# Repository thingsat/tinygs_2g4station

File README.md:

# TinyGS :: 2.4 GHz LoRa (low cost and low tech) ground station

Project to develop a ground station board that will receive messages from satellite on the 2.4GHz band. Satellite tracks are [Thingsat@STORK1](https://tinygs.com/satellite/ThingSat) and other cubeseat followed by the TinyGS community. This station is low cost (off the shelves boards and modules) and low tech (required only a solder iron).

This Git contains Hardware and software of a TinyGS 2.4 GHz LoRa ground station https://tinygs.com/.

## ESP32 Wroon 32U

The default MCU board is the [ESP32 Wroom 32U](https://www.espressif.com/sites/default/files/documentation/esp32-wroom-32d_esp32-wroom-32u_datasheet_en.pdf).

> Remark: The ESP32 Wroom 32D (on board PCB antenna) and The ESP32 Wroom 32U (UFL connector for an mandatory external antenna) can be used.

## SX1280 modules

For the long-range communication, we will use the Semtech SX1280, which is a low power 2.4 GHz LoRa RF Transceiver.

Several manufacturers provide RF modules integrating the SX1280 transceiver :
* [Lambda80 module](https://fr.farnell.com/rf-solutions/lambda80-24s/transceiver-2mbps-2-5ghz/dp/2988571)
* [EByte E28 module](https://www.amazon.com/Ebyte-%C3%89metteur-r%C3%A9cepteur-Bluetooth-E28-2G4M12S-%C3%A9metteur/dp/B07P2BZW5C)
* [SX1280PATR24 module](https://fr.aliexpress.com/item/1005001598235704.html) 
* [Miromico FMLR STM SX1280 module](https://miromico.ch/portfolio/fmlr-8x-x-stlx/?lang=en)
* [NiceRF LoRa1280 module](https://www.nicerf.com/products/detail/2-4ghz-lora-wireless-transceiver-module-lora1280-lora1281.html)
* [NiceRF LoRa1280-TCXO module](https://www.nicerf.com/products/detail/2-4ghz-range-measurement-wirelessly-long-distance-module-lora1280-tcxo.html)
* [NiceRF LoRa1280F27-TCXO module](https://www.nicerf.com/products/detail/500mw-2-4ghz-lora-wireless-transceiver-module-lora1280f27-tcxo.html)
* [Embit EMB-LR1280S](http://www.embit.eu/products/wireless-modules/emb-lr1280s/)

Project contains several PCBs and firmwares. 

##  Main Board

PCB are made to integrate up to 2 Mikrobus modules including SX1280 technology. Mikrobus board is an add-on board socket standard made by [mikroe](https://www.mikroe.com/mikrobus). This makes the ground station adjustable and modular.

There are 2 different PCB version:
* Board_Tinysgs_2.4GHz_V1, which contains: ESP32 Wroom 32 + 2 Mikrobus modules + Grove connectors (RXTX,I2C,ANA)
* Board_Tinysgs_2.4GHz_V2, which contains: ESP32 Wroom 32 + 2 Mikrobus modules + Grove connectors (RXTX,I2C,ANA) + H-Bridges for driving stepper + Power supply

We made the board as modular as possible. It is possible to implement all modules as desired, as long as it respects the Mikrobus pin specification. Mikrobus module are connected by SPI, I2C, UART and more GPIO. They are both supplied by 3V and Mikrobus_1 is also supplied by 5V if desired. 2 SMA connector mount edge are available on board. Theyre a connected to a SMA male connector, which allows to plug any signal that we want through a SMA female connector.

Both Mikrobus boards are connected to the ESP 32 by SPI. They are using the same SPI bus (SPI_0).

PCB are made on [KiCad](https://www.kicad.org/), which is a free software for electronics circuit board design. PCBs has been manufactered by [JLCPCB](https://jlcpcb.com/).

##  Power

A [Power Bank NCR18650B Battery shield](https://www.amazon.com/Diymore-Lithium-Battery-Charging-Arduino/dp/B07SZKNST4) made for Arduino and ESP32 can be plugged under the board using the 4 screw holes.

##  Mikrobus adapters for SX1280 modules

The design of two Mikrobus adapters for SX1280 modules are currently provided by the project:

* [Lambda80 SX1280 module adapter](./Mikrobus_Board_Lambda80C/)
* [EByte E28 SX1280 module adapter](./Mikrobus_Board_EbyteE28/)
* [NiceRF_SX1280_TCXO SX1280 module adapter](./Board_Mikrobus_NiceRF_1280_TCXO/)

The pinouts of those adapters have some differences.

> Two versions of the E28 module exists: 12S & 20S

```
EByte28 module
AN  <-> Busy
INT <-> DIO1
PWM <-> DIO2

Lambda80C module
AN  <-> DIO1
INT <-> Busy
PWM <-> DIO2

NiceRF SX1280 TCXO module
AN  <-> ??
INT <-> ??
PWM <-> ??
```

##  Other Mikrobus adapters for SX1280 modules

* [ ] [Geditech](https://www.geditech.fr/)'s LoRa SX1280 adapter
* [ ] [Stuart Robinson's (GW7HPW) Breadboard Friendly Board for NiceRF SX1280 Module](https://www.tindie.com/products/stuartsprojects/breadboard-friendly-board-for-nicrf-sx1280-module/)
* [ ] [Stuart Robinson's (GW7HPW) Breadboard Friendly Board for Ebyte E28 Module](https://www.tindie.com/products/stuartsprojects/breadboard-friendly-board-for-ebyte-e28-module/)

## Other Mikrobus modules (for the second Mikrobus slot)

Have a look into the [shop](https://www.mikroe.com/shop)

* [ ] [Geditech](https://www.geditech.fr/)'s LoRa Microchip RN2483 (for 433 MHz and 868 MHz ISM bands)

## Firmware

Firmware are into [./Firmware](./Firmware).

## Off-the-shelves gateways for LoRa 2.4 GHz

Those gateways had 3 LoRa® 2.4GHz channels for Rx and 1 LoRa® 2.4GHz channels for Tx.

* [Multitech MTCDT + MCard MTAC-LORA-2G4-3](https://www.multitech.net/developer/software/lora/mtac-lora-2g4-3/)
* [SX1280Z3DSFGW1 LoRa® 2.4GHz 3 Channels Single SF Reference Design](https://fr.semtech.com/products/wireless-rf/lora-24ghz/sx1280zxxxxgw1) (included a removable mPCIe card).
* [Embit EMB-FEM2GW-O-2G4](http://www.embit.eu/products/gateways-2/emb-fem2gw-o-2g4/) (included a removable mPCIe card EMB-LR1280-mPCIe-4x).

## References

* [ESP32-DevKitC V4 Getting Started Guide](https://docs.espressif.com/projects/esp-idf/en/latest/esp32/hw-reference/esp32/get-started-devkitc.html)
* [ESP32 Wroom 32 D/U Datasheet](https://www.espressif.com/sites/default/files/documentation/esp32-wroom-32d_esp32-wroom-32u_datasheet_en.pdf)

## Buy

### ESP32 Wroon 32U

* [ESP32-DevKitC-32U @ Aliexpress](https://fr.aliexpress.com/wholesale?SearchText=ESP32+Wroom+32U)
* [ESP32-DevKitC-32U @ Mouser](https://www.mouser.fr/ProductDetail/Espressif-Systems/ESP32-DevKitC-32U?qs=%252BEew9%252B0nqrCEVvpkdH%2FG5Q==)
* [ESP32-DevKit-LiPo @ Olimex](https://www.olimex.com/Products/IoT/ESP32/ESP32-DevKit-LiPo/open-source-hardware)

> **Important: ESP32 Wroon 32U had 38 pins and an UFL connector for an external (high gain and directive) antenna. ESP32 Wroon 32D had 38 pins and a PCB antenna. Choose ESP32 Wroon 32U for a better link margin.**

### SX1280 modules

* [LAMBDA80C-24D @ Farnell](https://fr.farnell.com/rf-solutions/lambda80c-24d/transceiver-2mbps-2-5ghz/dp/2988574?st=lambda80) (UFL connector + EM shield)
* [LAMBDA80C-24S @ Mouser](https://www.mouser.fr/ProductDetail/RF-Solutions/LAMBDA80C-24S?qs=17u8i%2FzlE89dhjIrlJ9FHg%3D%3D) (UFL connector + EM shield)
* [EByte E28-2G4M20S @ Aliexpress](https://fr.aliexpress.com/item/1005001812057589.html) (UFL connector + EM shield)

### PCB

* [Wuerth Elektronik](https://www.we-online.com/web/fr/wuerth_elektronik/start.php) 
* [JLCPCB](https://jlcpcb.com/)

### Headers and connectors
* [20-pin stackable headers (x2)](https://www.mouser.fr/ProductDetail/SparkFun/PRT-14311?qs=sGAEpiMZZMv0NwlthflBiwoz7B0w9MUDoIB50flBSMs%3D) for ESP32 : should be resized to 19 pins.
* [8-pin stackable headers (x2)](https://www.mouser.fr/ProductDetail/SparkFun/PRT-10007?qs=sGAEpiMZZMvShe%252BZiYheitG2EllKzxS98FBwaVjriqQ%3D) for Mikrobus modules.
* [Grove connectors (x3 but optional)](https://www.mouser.fr/ProductDetail/Seeed-Studio/110990030?qs=1%252B9yuXKSi8Dw9fpnq%252BdNzQ%3D%3D).

### Power (Optional)
* [Diymore 2x18650 Battery Pack @ Aliexpress](https://fr.aliexpress.com/item/33016661427.html)
* [DFRobot Solar Power Manager 5V](https://www.dfrobot.com/product-1712.html)
* [DFRobot Solar Power Manager Micro](https://www.dfrobot.com/product-1781.html)
* [Adafruit Universal USB / DC / Solar Lithium Ion/Polymer charger - bq24074](https://learn.adafruit.com/adafruit-bq24074-universal-usb-dc-solar-charger-breakout/design-notes)

### Power Profiling
* [Nordic Power Profiler Kit II](https://github.com/CampusIoT/tutorial/tree/master/nrf-ppk2#readme)
> Plug the PPK2 power source (`VOUT`+`GND`) on `3V3`+`GND` pin (double-row header and Grove connectors) and DO NOT plug the ESP32 throught the mini-USB connector.

### Debbuging
* [ ] [Click Analyzer](https://www.mikroe.com/click-analyzer)

## 2.4 GHz antennas
* [SuperAntennaz](https://wiki.satnogs.org/SuperAntennaz)
* [DIY Quadrifilar Helix Antenna for 2450 MHz](https://www.thingiverse.com/thing:634205)
* [Sirio SDC-2.4-15](https://www.sirioantenne.it/en/products/wlan/sdc-2-4-15): Directional, Linear Vertical or Horizontal Polarization, 12.9 dBd – 15 dBi.
  
## Licenses

For PCB designs, the license is [Attribution-NonCommercial-ShareAlike 4.0 International (CC BY-NC-SA 4.0)](https://creativecommons.org/licenses/by-nc-sa/4.0/).

For Software, check the license into each directory.

## Todolist

* [x] PCB for ESP32 Wroom 32 (38 pins) + 2 Mikrobus modules + 3 groves connectors (RXTX,I2C,ANA)
* [ ] PCB for ESP32 Wroom 32 (38 pins) + 2 Mikrobus modules + 3 groves connectors (RXTX,I2C,ANA) + H-Bridges for driving stepper + Power supply
* [x] Mikrobus adapter for Lambda80 SX1280 module
* [x] Mikrobus adapter for EByte E28 SX1280 module
* [ ] Mikrobus adapter for [SX1280PATR24 module](https://fr.aliexpress.com/item/1005001598235704.html) 
* [ ] Mikrobus adapter for [Miromico FMLR STM SX1280 module](https://miromico.ch/portfolio/fmlr-8x-x-stlx/?lang=en)
* [ ] Mikrobus adapter for [NiceRF SX1280 module](https://stuartsprojects.github.io/2019/10/07/2-4ghz-nicerf-sx1280-lora-balloon-tracker-85km-achieved.html)
* [ ] Mikrobus adapter for [Microchip RN2483 module](https://www.microchip.com/en-us/product/RN2483)
* [ ] Mikrobus adapter for [RF Solutions RF-LORA-868-SO module](https://fr.rs-online.com/web/p/lpwan/9033059)
* [ ] Mikrobus adapter for [Abeeway-Murata Geolocation Module](https://docs.abeeway.com/thingpark-location/B-Feature-Topics/GeolocModule_C/)
* [ ] Mikrobus protoshield
* [x] [Arduino sketches](./Firmware/Arduino/SX1280) for ESP32 Wroom 32 + E28 Mikrobus module
* [x] [Arduino sketches](./Firmware/Arduino/SX1280) for ESP32 Wroom 32 + Lambda80 Mikrobus module
* [ ] [Arduino sketches](./Firmware/Arduino/SX1280) for Wio Terminal + Lambda80 Mikrobus module
* [ ] Move UART Grove connector for using Grove cable with ESP32-WROOM-32D (PCB antenna)
* [ ] TinyGS firmware for ESP32 Wroom 32 + E28 Mikrobus module
* [ ] TinyGS firmware for ESP32 Wroom 32 + Lambda80 Mikrobus module
* [ ] TinyGS firmware for ESP32 Wroom 32 + [Miromico FMLR STM SX1280 module](https://miromico.ch/portfolio/fmlr-8x-x-stlx/?lang=en)
* [ ] TinyGS firmware for ESP32 Wroom 32 + [LR1120 Dev Kit module](https://fr.semtech.com/products/wireless-rf/lora-edge/lr1120dvk1tbks) for such modulations and bands : LoRa SubGHz, LoRa 2.4GHz, LR-FHSS, S-Band (1.9-2.1GHz)
* [ ] TinyGS firmware for [Wio Terminal](https://wiki.seeedstudio.com/Wio-Terminal-Getting-Started/) + Lambda80 Mikrobus module
* [ ] Power consumption study with [X-NUCLEO-LPM01A](https://www.st.com/en/evaluation-tools/x-nucleo-lpm01a.html)
* [ ] RIOTOS firmware for ESP32 Wroom 32 + Lambda80 module (cubesat emulator)
* [ ] Test the [Geditech](https://www.geditech.fr/)'s LoRa Microchip RN2483 (for 433 MHz and 868 MHz ISM bands) on second slot.
* [ ] Add slots for I2C and UART grove connectors into the two Mikrobus slots (can be used when the Mikrobus slot is not used)
* [ ] Add slot for female header in order to plug a low-cost SDCard SPI breakout (useful for data logging)
* [ ] Add slot for female/male header in order to plug a low-cost DS1307/DS3231 breakout (useful for timestamping data log entries)
* [ ] Add extra slot for power sources (3V3, VCC)
* [ ] Add white label for DevEUI and serial number on silkscreen layer
* [ ] Add pin for IRQ on [GNSS PPS](https://en.wikipedia.org/wiki/Pulse-per-second_signal)
* [ ] Design Fritzing part for the station
* [x] add licenses
* [ ] review PCB designs according the [Mikrobus specifications v2.0](https://download.mikroe.com/documents/standards/mikrobus/mikrobus-standard-specification-v200.pdf)
* [ ] add L9616 CAN driver footprint ([see](https://copperhilltech.com/blog/can-bus-development-with-esp32wroom32-development-board/)) connected to `CAN_TXD = ESP32 – IO25` and `CAN_RXD = ESP32 – IO26`

## Media

Here the picture of the board_V1, with or without modules. On last picture, a GPS, a magnetometer and a joystick are connected by grove connection.

Mounted PCB with Grove boards ([Grove Thumb Joystick](https://wiki.seeedstudio.com/Grove-Thumb_Joystick/), [Grove  LSM6DS3 Accelerometer Gyroscope](https://wiki.seeedstudio.com/Grove-6-Axis_AccelerometerAndGyroscope/), [Grove GPS](https://wiki.seeedstudio.com/Grove-GPS/)) and Lamdba80 and E28 module.

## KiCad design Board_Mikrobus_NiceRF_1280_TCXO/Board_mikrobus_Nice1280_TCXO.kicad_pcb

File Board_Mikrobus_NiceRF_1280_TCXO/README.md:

# Mikrobus adapter for [NiceRF 1280 TCXO module](https://www.nicerf.com/sx1280/)

Designed by [Nicolas Nohlier](https://www.linkedin.com/in/nicolas-nolhier-127b4a61/?originalSubdomain=fr) ([F5MDY](https://fr.aprs.fi/info/a/F5MDY-B)), [CSUT](https://www.csut.cnrs.fr/) & LAAS.

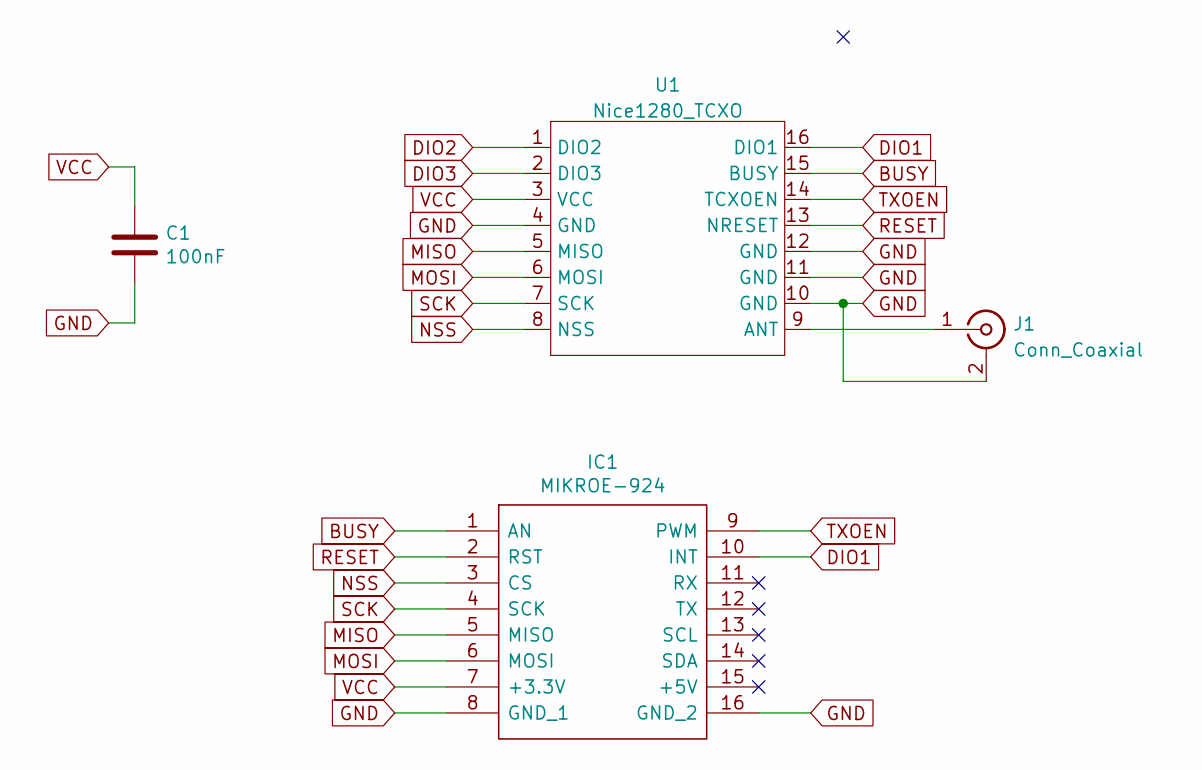
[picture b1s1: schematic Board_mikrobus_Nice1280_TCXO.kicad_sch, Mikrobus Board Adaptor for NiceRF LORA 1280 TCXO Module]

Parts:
C1: 100nF; C_0805_2012Metric_Pad1.18x1.45mm_HandSolder
IC1: MIKROE-924; MIKROE924; Manufacturer_Part_Number MIKROE-924; Mouser Part Number 932-MIKROE-924
J1: Conn_Coaxial; U.FL_Molex_MCRF_73412-0110_Vertical
U1: Nice1280_TCXO; HOPERF_RFM9XW_SMD

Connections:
BUSY: IC1.1 (AN), U1.15 (BUSY)
DIO1: IC1.10 (INT), U1.16 (DIO1)
DIO2: U1.1 (DIO2)
DIO3: U1.2 (DIO3)
GND: C1.2, IC1.8 (GND_1), IC1.16 (GND_2), J1.2 (Ext), U1.4 (GND), U1.10 (GND), U1.11 (GND), U1.12 (GND)
MISO: IC1.5 (MISO), U1.5 (MISO)
MOSI: IC1.6 (MOSI), U1.6 (MOSI)
NSS: IC1.3 (CS), U1.8 (NSS)
unnamed: J1.1 (In), U1.9 (ANT)
RESET: IC1.2 (RST), U1.13 (NRESET)
SCK: IC1.4 (SCK), U1.7 (SCK)
TXOEN: IC1.9 (PWM), U1.14 (TCXOEN)
VCC: C1.1, IC1.7 (+3.3V), U1.3 (VCC)

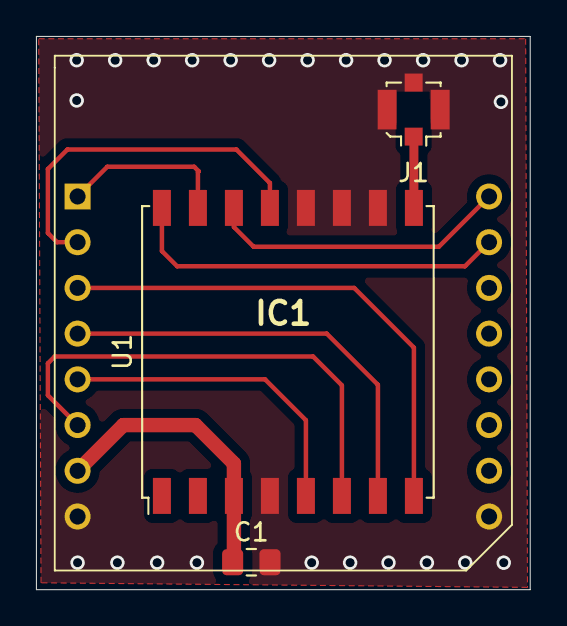
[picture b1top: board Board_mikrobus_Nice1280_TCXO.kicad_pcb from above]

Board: 2 copper layers, 27.4 x 30.7 mm, 4 parts (0 on the bottom side), 11 nets.

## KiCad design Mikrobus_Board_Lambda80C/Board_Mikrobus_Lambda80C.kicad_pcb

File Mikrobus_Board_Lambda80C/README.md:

# Mikrobus Adapter for Lambda80-24S SX1280 Module

This is a board to support a lambda80C 2.4GHz LORA transceiver RF module, adapted to Mikrobus standard pinout specification.

Lambda Module used: [Lambda80-24S](https://fr.farnell.com/rf-solutions/lambda80-24s/transceiver-2mbps-2-5ghz/dp/2988571). The LAMBDA80 is a 2.4GHz LoRa transceiver using the Semtech SX1280 technology, providing ultra-long range, spread spectrum communication and high interference immunity within minimal current. For more information on [SX1280](https://github.com/thingsat/tinygs_2g4station/blob/main/Datasheet_SEMTECH_SX1280.PDF).

Some Specification:
* Transmit power +12.5 dBm
* High sensitivity: down to -132 dBm
* RF Data Rate: FSK upto 2.02Mbps - LoRa upto 476bps

Programing of the module is via SPI interface. This module has as pin BUSY, RESET, SPI, 3 DIO (Digital I/O software configured) and a Antenna connection “C” Versions. Antenna  is connectable with a connector UFL female.

Here the connection between the Mikrobus standard pin and the Lambda80 module pin

	AN	<->	DIO1
	RST	<->	RESET
	CS	<->	NSEL
	SCK	<->	SCLK
	MISO	<->	SDO
	MOSI	<->	SDI
	PWM	<->	DIO2
	INT	<->	BUSY

Lambda80 is supplied with 3.3V, by the +3.3V Mikrobus pin.

The Ebyte E28 module has no PCB antenna, so a external antenna is needed. A UFL male connector is available on the module to plug a external antenna with a UFL female connector.

### Kicad Project
The project was made on Kikad, which is a free software for electronics circuit board design, developed by IUT of Grenoble.

For the mikrobus lib and footprint, I use the [MIKROE-924](https://componentsearchengine.com/part-view/MIKROE-924/MIKROELEKTRONIKA) model available on [component search engine](https://componentsearchengine.com/).
For the Lambda80, I use the [Lambda80](https://componentsearchengine.com/part-view/LAMBDA80-24S/RF%20SOLUTIONS) model.

All the schematic and footprint are in the "Lib & Fp" folder. For the Mikrobus and Lambda80 lib, you have to choose the KiCad folder when adding the lib to the project.

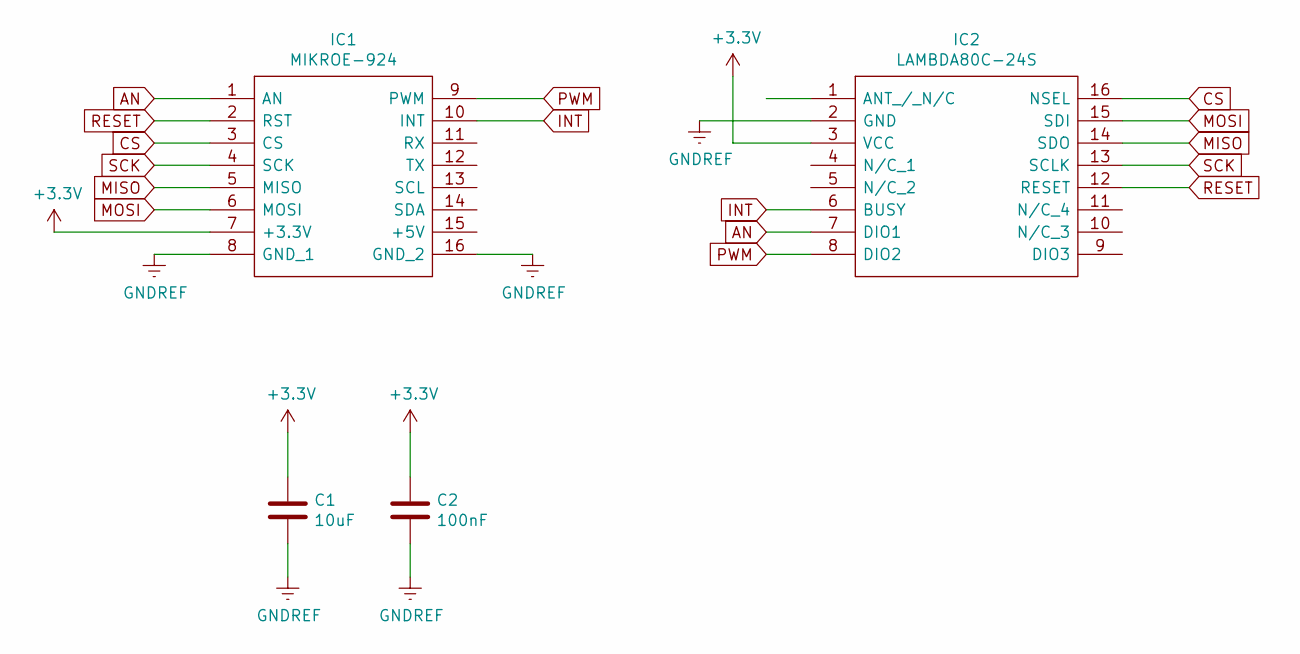
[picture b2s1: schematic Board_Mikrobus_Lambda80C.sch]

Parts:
C1: 10uF; C_0805_2012Metric
C2: 100nF; C_0805_2012Metric
IC1: MIKROE-924; MIKROE924; Manufacturer_Part_Number MIKROE-924; Mouser Part Number 932-MIKROE-924
IC2: LAMBDA80C-24S; Lambda80C_24S-traversant; Manufacturer_Part_Number LAMBDA80C-24S; Mouser Part Number 223-LAMBDA80C-24S

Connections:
+3V3: C1.1, C2.1, IC1.7 (+3.3V), IC2.3 (VCC)
AN: IC1.1 (AN), IC2.7 (DIO1)
CS: IC1.3 (CS), IC2.16 (NSEL)
GNDREF: C1.2, C2.2, IC1.8 (GND_1), IC1.16 (GND_2), IC2.2 (GND)
INT: IC1.10 (INT), IC2.6 (BUSY)
MISO: IC1.5 (MISO), IC2.14 (SDO)
MOSI: IC1.6 (MOSI), IC2.15 (SDI)
PWM: IC1.9 (PWM), IC2.8 (DIO2)
RESET: IC1.2 (RST), IC2.12 (RESET)
SCK: IC1.4 (SCK), IC2.13 (SCLK)

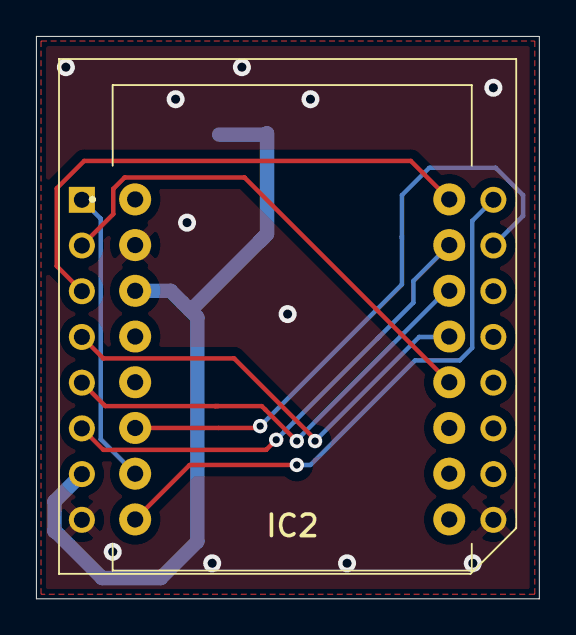
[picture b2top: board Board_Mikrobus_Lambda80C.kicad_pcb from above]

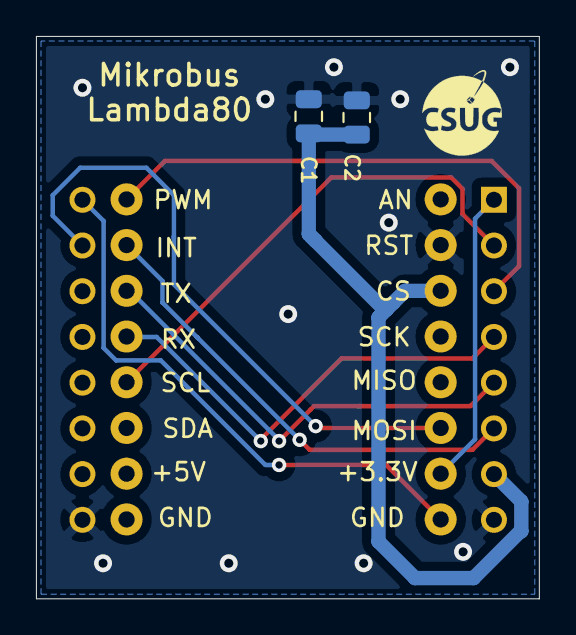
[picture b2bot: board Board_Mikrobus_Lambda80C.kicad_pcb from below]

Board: 2 copper layers, 27.9 x 31.2 mm, 4 parts (2 on the bottom side), 10 nets.

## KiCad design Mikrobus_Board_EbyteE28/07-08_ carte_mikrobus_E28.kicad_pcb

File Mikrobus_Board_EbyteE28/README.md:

# Mikrobus Adapter for Ebyte E28 SX1280 Module

This is a board to support a Ebyte E28 2.4GHz LORA transceiver RF module, adapted to Mikrobus standard pinout specification. This board will allow you to use your Ebyte E28-2G4M module with a standard 0.1” matrix breadboard or a Mikrobus Standard.

The Ebyte E28-2G4M is a RF transceiver module using the Semtech SX1280 LoRa technology, operate in 2.400 ~ 2.500GHz with ultra-low power consumption. More information available on [Ebyte site](https://www.ebyte.com/en/product-view-news.html?id=286). 

This board can support E28_2G4M12S and E28_2G4M20S. This Ebyte E28 Board is inspired by the [Breadboard Friendly Ebyte E28 Board](https://github.com/StuartsProjects/Devices/tree/master/Breadboard%20Friendly%20EbyteE28%20Board) made by StuartsProjects.

Ebyte E28 module usable: [Ebyte E28-2G4M12S](https://www.amazon.fr/Ebyte-%C3%89metteur-r%C3%A9cepteur-Bluetooth-E28-2G4M12S-%C3%A9metteur/dp/B07P2BZW5C) / [Ebyte E28-2G4M20S](https://www.amazon.fr/EBYTE-E28-2G4M20S-SX1280-%C3%89metteur-R%C3%A9cepteur/dp/B07R77CKFK). They are the same module, exept that the E28-2G4M20S as 2 more Pins (14 pin for 12S and 16 pin for 20S).These extra pins are for Rx/Tx connection for PA and LNA control.

Here the connection between the Mikrobus standard pin and the E28 module pin

	AN	<->	Busy
	RST	<->	NRESET
	CS	<->	NSS_CTS
	SCK	<->	SCK_RTS
	MISO	<->	MISO_TX
	MOSI	<->	MOSI_RX
	PWM	<->	DIO2
	INT	<->	DIO1
	
	for M20S
	Rx	<->	TX_EN
	Tx	<->	RX_EN

Ebyte E28 is supplied with 3.3V, by the +3.3V Mikrobus pin.

The Ebyte E28 module has a PCB antenna, so no external antenna is needed, but the here also a SMA connector to use a external antenna.

## Kicad Project
The project was made on Kikad, which is a free software for electronics circuit board design, developed by IUT of Grenoble.

For the mikrobus lib and footprint, I use the [MIKROE-924](https://componentsearchengine.com/part-view/MIKROE-924/MIKROELEKTRONIKA) model available on [component search engine](https://componentsearchengine.com/).
For the E28 schematic and footprint, I found nothing on internet so I made my own. 

All the schematic and footprint are in the "Lib & Fp" folder. For the Mikrobus lib, you have to choose the KiCad folder.

## TODO

* [ ] Move module in order to place the PCB antenna outside of the adapter.

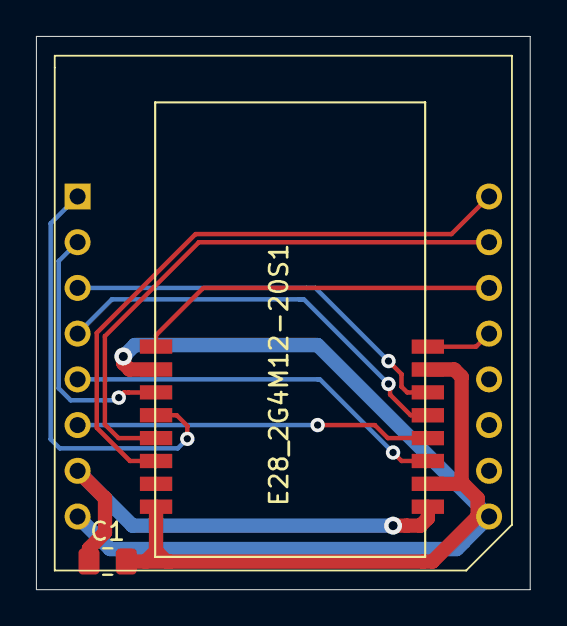
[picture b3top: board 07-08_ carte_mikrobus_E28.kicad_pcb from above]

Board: 2 copper layers, 27.4 x 30.7 mm, 3 parts (0 on the bottom side), 12 nets.

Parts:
C1: 100nF; C_0805_2012Metric_Pad1.18x1.45mm_HandSolder
E28_2G4M12-20S1: E28; E28-2G4M12-20S
IC1: MIKROE-924; MIKROE924

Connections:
BUSY: E28_2G4M12-20S1.12, IC1.1
DIO1: E28_2G4M12-20S1.13, IC1.10
DIO2: E28_2G4M12-20S1.14, IC1.9
GND: C1.2, E28_2G4M12-20S1.2, E28_2G4M12-20S1.7, E28_2G4M12-20S1.10, E28_2G4M12-20S1.16, IC1.8, IC1.16
MISO: E28_2G4M12-20S1.3, IC1.5
MOSI: E28_2G4M12-20S1.4, IC1.6
NSS: E28_2G4M12-20S1.6, IC1.3
RESET: E28_2G4M12-20S1.11, IC1.2
RXEN: E28_2G4M12-20S1.8, IC1.12
SCK: E28_2G4M12-20S1.5, IC1.4
TXEN: E28_2G4M12-20S1.9, IC1.11
VCC: C1.1, E28_2G4M12-20S1.1, IC1.7

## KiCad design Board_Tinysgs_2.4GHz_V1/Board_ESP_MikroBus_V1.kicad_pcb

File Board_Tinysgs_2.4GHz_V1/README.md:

# Main Board for TinyGS 2.4GHz Station

This board is the firts version of the 2.4GHz gateway for [TinyGS](https://tinygs.com/).

Contain Schematic and PCB file for ESP32 Vroom + 2 Mikrobus modules + 2 groves connectors (RXTX,I2C).

This Board is designed to support a ESP32 devkitC-V4 and 2 MiKroBus modules. This board is the firts version of the 2.4GHz tinygs ground station gateway and named Board_V1

The purpose of this board is to control mikrobus modules including SX1280 technology that will transmit and receive messages on a 2.4GHz radio frequency. Each module are connected to a ESP32 which will be connected to the wifi.

Mikrobus board is an add-on board socket standard made by [mikroe](https://www.mikroe.com/mikrobus)

Connection between ESP32 - ESP32-DevKitC V4 and Mikrobus modules

MiKroBus 0:
	 				 
	SPI_0:
	CLK 	IO18
	MISO	IO19
	MOSI	IO23
	NSS(CS)	IO05
	
	UART_0	:
	Tx	IO01
	Rx	IO03
	
	I2C:
	SDA	IO21
	SCL	IO22
	
	AN_0	IO33
	RESET_0 IO32
	PWM_0	IO25
	INT_0	IO26

MiKroBus 1: 				 
	
	SPI_0
	CLK 	IO18
	MISO	IO19
	MOSI	IO23
	NSS 	IO15
	
	UART_2
	Tx	IO17
	Rx	IO16
	
	I2C:
	SDA	IO21
	SCL	IO22
	
	AN_1	IO27
	RESET_1 IO14
	PWM_1	IO04
	INT_1	IO13

Grove connector available on board :

	I2C:			UART_2(Rx/Tx):		GPIO(INPUT Only):
	SDA   IO21		Tx	IO17		IO34
	SCL   IO22		Rx	IO16		IO35

UART_2 can be connected to module MiKroBus 2 or to grove connector. A jumper need to be plug to choose beetween grove output or the mikrobus module.

Two UFL connected to a SMA mount edge connector are available to plug an antenna. They are disconnected from the rest of the board, which allows to connect the module that you want to the antenna, with a SMA -UFL connector.

A powerbank can be plug under the board to supply the 3V. The [powerbank](https://www.amazon.com/Diymore-Lithium-Battery-Charging-Arduino/dp/B07SZKNST4) is design for ESP32 and is purchasable on amazon. 
5V is only available on the Mikrobus 1 module. 

Careful:
* UART0 is used for flashing and debuging. Be very careful to its use.
* GPIO grove connector are INPUT only, ESP32wroom cannot write on this connection.
* Both Chip selec (NSS) for the SPI communication are Pulled HIGH (IO05 & IO15).
* No 5V on Mikrobus 0. 

## Library and footprint

Lib & empreinte folder contains all necessary symbol and footprint for the project:
* ESP32 symbol and footprint. Footprint has been changed to match with our ESP32-devkitC-V4
* Mikrobus (mikroe-2439) symbol and footprint
* Grove connector for I2C and RxTx connection
* SMA and UFL connector

## Files
* .pro: File containing the parameters of the project.
* .sch: Schema files.
* .kicad_pcb: Printed circuit board files.
* sym-info-cache: Library list file (symbol library table): declaration of component symbol libraries available for the schema editor.
* fp-lib-table: Library list file (footprint library table): declaration of component footprint libraries available for the PCB editor.

## Rendered

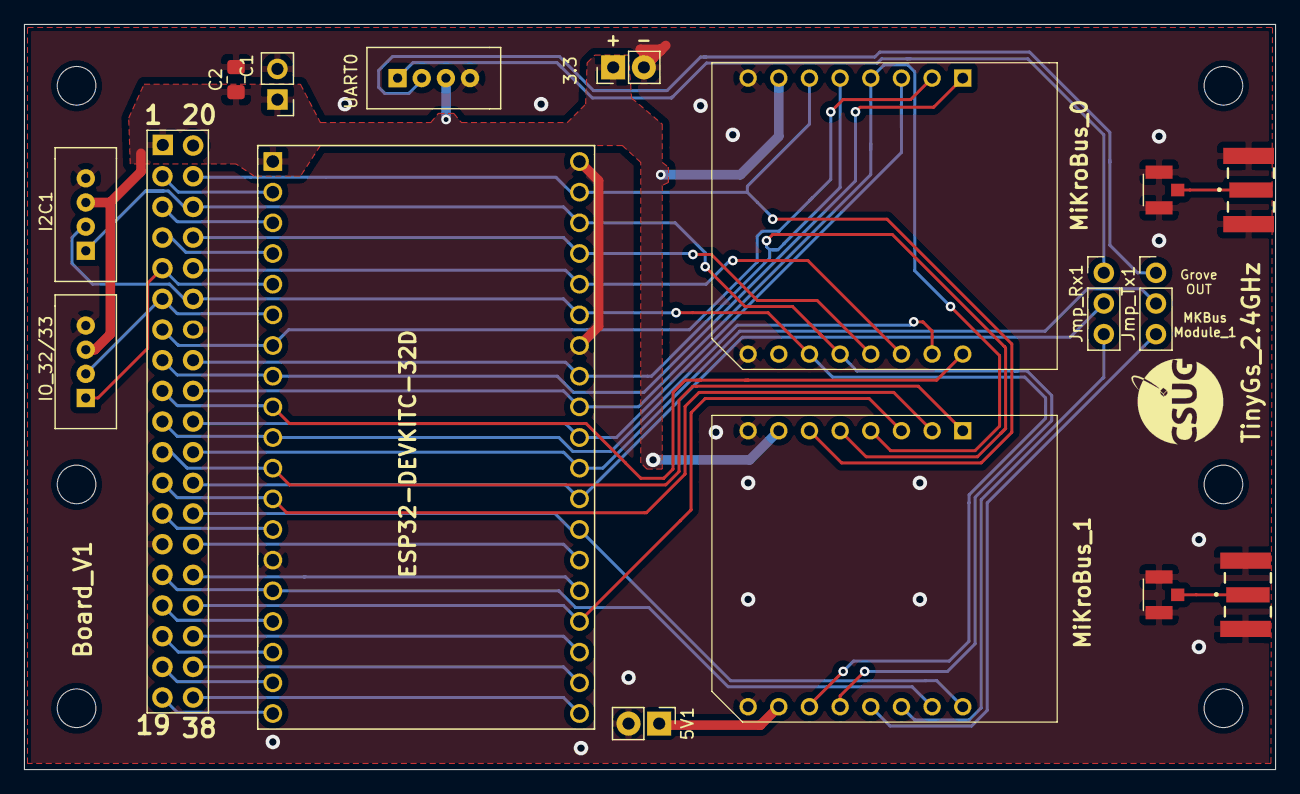
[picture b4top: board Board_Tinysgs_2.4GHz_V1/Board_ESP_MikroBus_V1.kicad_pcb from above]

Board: 2 copper layers, 103.6 x 61.7 mm, 17 parts (0 on the bottom side), 43 nets.

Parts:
3.3, 5V1: Conn_01x02; PinHeader_1x02_P2.54mm_Vertical
C1: C; PinHeader_1x02_P2.54mm_Vertical
C2: C; C_0805_2012Metric_Pad1.18x1.45mm_HandSolder
Connector_2x19: Conn_02x19_Top_Bottom; conn_2x19_2.54mm_top_bot
I2C1: Grove; Grove_4pin-2.00mm
IO_32/33: Grove; Grove_4pin-2.00mm
Jmp_Rx1: Jumper_NC_Dual; PinHeader_1x03_P2.54mm_Vertical
Jmp_Tx1: Jumper_NC_Dual; PinHeader_1x03_P2.54mm_Vertical
MiKroBus_0, MiKroBus_1: MIKROE-924; MIKROE924
SMA_1, SMA_2: SMA-J-P-H-ST-EM1; SAMTEC_SMA-J-P-H-ST-EM1
U1: ESP32-DEVKITC-32D; MODULE_ESP32-DEVKITC-V4-32D
UART0: Grove; Grove_4pin-2.00mm
UFL_1, UFL_2: U.FL-R-SMT(01); HRS_U.FL-R-SMT(01)

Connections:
+3V3: 3.3.1, C1.1, C2.1, Connector_2x19.1, I2C1.3, IO_32/33.3, MiKroBus_0.7, MiKroBus_1.7, U1.1, UART0.3
+5V: 5V1.1, MiKroBus_1.15
/2: Connector_2x19.2, U1.2
/3: Connector_2x19.3, U1.3
/4: Connector_2x19.4, U1.4
/13: Connector_2x19.13, U1.13
/16: Connector_2x19.16, U1.16
/17: Connector_2x19.17, U1.17
/18: Connector_2x19.18, U1.18
/19: Connector_2x19.19, U1.19
/33: Connector_2x19.33, U1.33
/34: Connector_2x19.34, U1.34
/36: Connector_2x19.36, U1.36
/37: Connector_2x19.37, U1.37
/38: Connector_2x19.38, U1.38
AN_0: Connector_2x19.8, MiKroBus_0.1, U1.8
AN_1: Connector_2x19.11, MiKroBus_1.1, U1.11
GNDREF: 3.3.2, 5V1.2, C1.2, C2.2, Connector_2x19.14, Connector_2x19.20, Connector_2x19.26, I2C1.4, IO_32/33.4, MiKroBus_0.8, MiKroBus_0.16, MiKroBus_1.8, MiKroBus_1.16, SMA_1.2_1, SMA_1.2_2, SMA_1.3_1, SMA_1.3_2, SMA_2.2_1, SMA_2.2_2, SMA_2.3_1, SMA_2.3_2, U1.14, U1.20, U1.26, UART0.4, UFL_1.1, UFL_1.2, UFL_2.1, UFL_2.2
I2C_SCL: Connector_2x19.22, I2C1.1, MiKroBus_0.13, MiKroBus_1.13, U1.22
I2C_SDA: Connector_2x19.25, I2C1.2, MiKroBus_0.14, MiKroBus_1.14, U1.25
IN34: Connector_2x19.5, IO_32/33.1, U1.5
IN35: Connector_2x19.6, IO_32/33.2, U1.6
INT_0: Connector_2x19.10, MiKroBus_0.10, U1.10
INT_1: Connector_2x19.15, MiKroBus_1.10, U1.15
MISO_0: Connector_2x19.27, MiKroBus_0.5, MiKroBus_1.5, U1.27
MOSI_0: Connector_2x19.21, MiKroBus_0.6, MiKroBus_1.6, U1.21
NSS_0: Connector_2x19.29, MiKroBus_0.3, U1.29
NSS_1: Connector_2x19.35, MiKroBus_1.3, U1.35
unnamed: SMA_1.1, UFL_1.3
unnamed: SMA_2.1, UFL_2.3
PWM_0: Connector_2x19.9, MiKroBus_0.9, U1.9
PWM_1: Connector_2x19.32, MiKroBus_1.9, U1.32
Reset_0: Connector_2x19.7, MiKroBus_0.2, U1.7
Reset_1: Connector_2x19.12, MiKroBus_1.2, U1.12
SCK_0: Connector_2x19.28, MiKroBus_0.4, MiKroBus_1.4, U1.28
UART0_Rx: Connector_2x19.24, MiKroBus_0.11, U1.24
UART0_Tx: Connector_2x19.23, MiKroBus_0.12, U1.23
UART2_Rx: Connector_2x19.31, Jmp_Rx1.2, U1.31
UART2_Rx_MiKroBus: Jmp_Rx1.3, MiKroBus_1.11
UART2_Rx_grove: Jmp_Rx1.1, UART0.1
UART2_Tx: Connector_2x19.30, Jmp_Tx1.2, U1.30
UART2_Tx_MiKroBus: Jmp_Tx1.3, MiKroBus_1.12
UART2_Tx_grove: Jmp_Tx1.1, UART0.2

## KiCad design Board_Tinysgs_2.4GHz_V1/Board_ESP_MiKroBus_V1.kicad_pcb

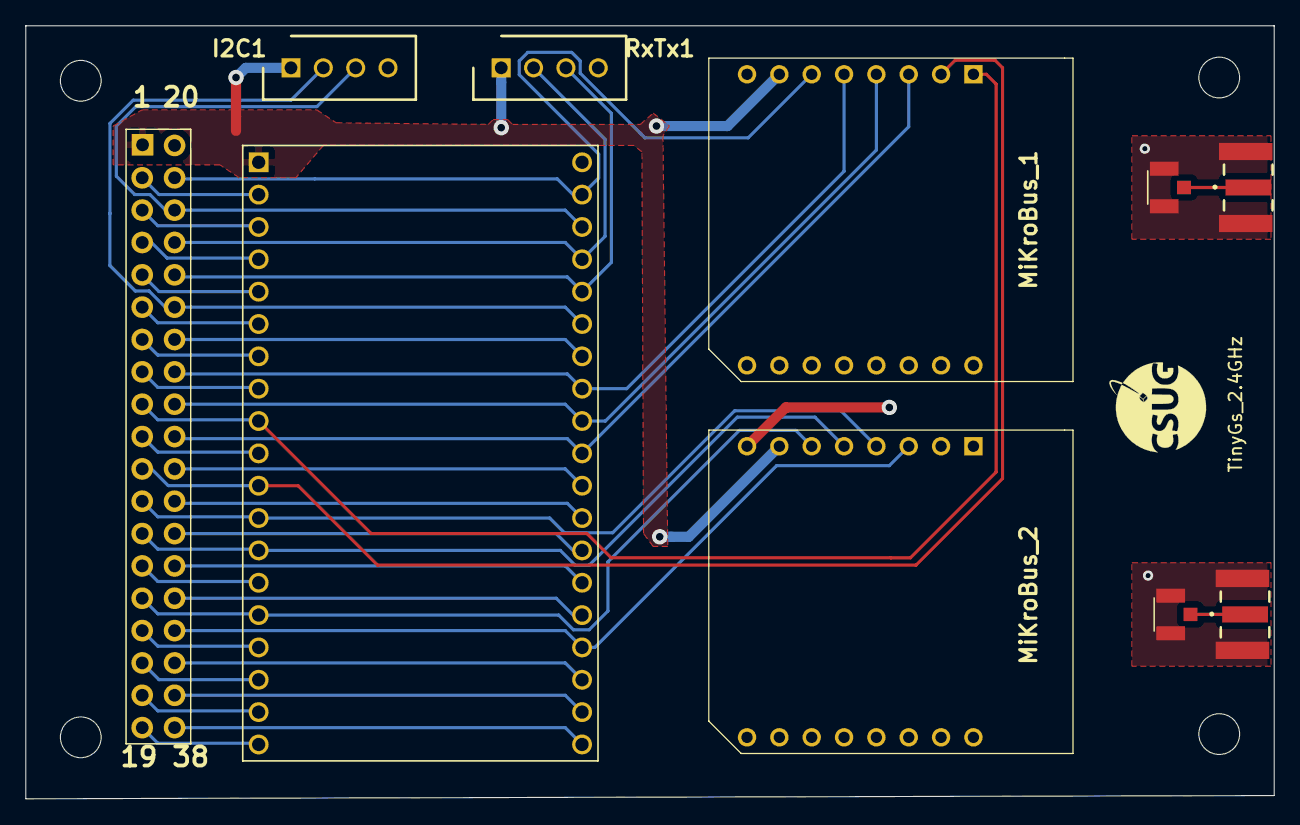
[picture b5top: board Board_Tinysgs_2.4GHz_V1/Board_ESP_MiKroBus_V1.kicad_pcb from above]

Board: 2 copper layers, 98.0 x 60.7 mm, 10 parts (0 on the bottom side), 40 nets.

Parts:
Connector_2x19: Conn_02x19_Top_Bottom; conn_2x19_2.54mm_top_bot
I2C1: Grove; HDRV4W80P0X254_1X4_1200X500X1550P
MiKroBus_1, MiKroBus_2: MIKROE-924; MIKROE924
RxTx1: Grove; HDRV4W80P0X254_1X4_1200X500X1550P
SMA_1, SMA_2: SMA-J-P-H-ST-EM1; SAMTEC_SMA-J-P-H-ST-EM1
U1: ESP32-DEVKITC-32D; MODULE_ESP32-DEVKITC-V4-32D
UFL_1, UFL_2: U.FL-R-SMT(01); HRS_U.FL-R-SMT(01)

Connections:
+3V3: Connector_2x19.1, I2C1.1, MiKroBus_1.7, MiKroBus_2.7, RxTx1.1, U1.1
/2: Connector_2x19.2, U1.2
/3: Connector_2x19.3, U1.3
/4: Connector_2x19.4, U1.4
/5: Connector_2x19.5, U1.5
/6: Connector_2x19.6, U1.6
/7: Connector_2x19.7, U1.7
/8: Connector_2x19.8, U1.8
/10: Connector_2x19.10, U1.10
/14: Connector_2x19.14, U1.14
/16: Connector_2x19.16, U1.16
/17: Connector_2x19.17, U1.17
/18: Connector_2x19.18, U1.18
/19: Connector_2x19.19, U1.19
/26: Connector_2x19.26, U1.26
/30: Connector_2x19.30, U1.30
/31: Connector_2x19.31, U1.31
/33: Connector_2x19.33, U1.33
/36: Connector_2x19.36, U1.36
/37: Connector_2x19.37, U1.37
/38: Connector_2x19.38, U1.38
GNDREF: Connector_2x19.20, I2C1.4, MiKroBus_1.8, MiKroBus_2.8, RxTx1.4, SMA_1.2_1, SMA_1.2_2, SMA_1.3_1, SMA_1.3_2, SMA_2.2_1, SMA_2.2_2, SMA_2.3_1, SMA_2.3_2, U1.20, UFL_1.1, UFL_1.2, UFL_2.1, UFL_2.2
I2C_SCL: Connector_2x19.22, I2C1.3, U1.22
I2C_SDA: Connector_2x19.25, I2C1.2, U1.25
LED_1: Connector_2x19.34, U1.34
LED_2: Connector_2x19.32, U1.32
MISO_0: Connector_2x19.27, MiKroBus_1.5, U1.27
MISO_1: Connector_2x19.13, MiKroBus_2.5, U1.13
MOSI_0: Connector_2x19.21, MiKroBus_1.6, U1.21
MOSI_1: Connector_2x19.15, MiKroBus_2.6, U1.15
NReset_0: Connector_2x19.11, MiKroBus_1.2, U1.11
NSS_0: Connector_2x19.29, MiKroBus_1.3, U1.29
NSS_1: Connector_2x19.35, MiKroBus_2.3, U1.35
unnamed: SMA_1.1, UFL_1.3
unnamed: SMA_2.1, UFL_2.3
RFBusy_0: Connector_2x19.9, MiKroBus_1.1, U1.9
SCK_0: Connector_2x19.28, MiKroBus_1.4, U1.28
SCK_1: Connector_2x19.12, MiKroBus_2.4, U1.12
UART_Rx: Connector_2x19.24, RxTx1.3, U1.24
UART_Tx: Connector_2x19.23, RxTx1.2, U1.23

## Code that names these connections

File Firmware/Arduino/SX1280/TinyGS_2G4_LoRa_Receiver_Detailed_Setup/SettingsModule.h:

//*******  Setup hardware pin definitions here ! ***************

//These are the pin definitions for TinyGS 2G4 mikrobus modules
// https://github.com/thingsat/tinygs_2g4station/tree/main/Board_Tinysgs_2.4GHz_V1


#define SCK       18                                  //SCK on SPI3
#define MISO      19                                  //MISO on SPI3 
#define MOSI      23                                  //MOSI on SPI3 

#define NSS_0     5                                   //select pin on LoRa device
#define NSS_1     15                                   //select pin on LoRa device

#define AN_0      33
#define RESET_0   32
#define PWM_0     25
#define INT_0     26

#define AN_1      27
#define RESET_1   14
#define PWM_1     04
#define INT_1     13



#if defined(MIKROBUS0_E28) || defined(MIKROBUS0_NICERF)

/*
E28 module
AN  <-> Busy
INT <-> DIO1
PWM <-> DIO2
*/

#define NSS     NSS_0
#define DIO1    INT_0                               //DIO1 pin on LoRa device, used for RX and TX done 
#define RFBUSY  AN_0                                //busy line
#define NRESET  RESET_0                     //reset pin on LoRa device


#elif defined(MIKROBUS1_E28) || defined(MIKROBUS1_NICERF)

/* same mapping but on port 1*/

#define NSS     NSS_1
#define DIO1    INT_1
#define RFBUSY  AN_1
#define NRESET  RESET_1


/* ********************* */

#elif defined(MIKROBUS0_LAMBDA80)

/*
Lambda80C module
AN  <-> DIO1
INT <-> Busy
PWM <-> DIO2
*/

#define NSS     NSS_0
#define DIO1    AN_0                                //DIO1 pin on LoRa device, used for RX and TX done 
#define RFBUSY  INT_0                               //busy line
#define NRESET  RESET_0                     //reset pin on LoRa device


#elif defined(MIKROBUS1_LAMBDA80)

/* same mapping but on port 1*/

#define NSS     NSS_1
#define DIO1    AN_1
#define RFBUSY  INT_1
#define NRESET  RESET_1



#else

#error Unknown module

#endif


#define LED1 2                                  //on board LED, high for on

#define DIO2  -1                                //DIO2 pin on LoRa device, normally not used so set to -1 
#define DIO3 -1                                 //DIO3 pin on LoRa device, normally not used so set to -1
#define RX_EN -1                                //pin for RX enable, used on some SX128X devices, set to -1 if not used
#define TX_EN -1                                //pin for TX enable, used on some SX128X devices, set to -1 if not used 
#define BUZZER -1                               //pin for buzzer, set to -1 if not used 
#define VCCPOWER 14                             //pin controls power to external devices

#define LORA_DEVICE DEVICE_SX1280               //we need to define the device we are using

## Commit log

2021-06-22 change title
2021-06-22 add todolist
2021-06-22 add todos
2021-06-25 Firts commit: PCB for ESP32 Vroom + 2 Mikrobus modules + 2 groves
2021-06-26 fix title
2021-06-30 Commit board_V1 + Lib + README
    Readme a completer.
2021-07-01 Adding images
    MiKroBus_Module: Main folder
    Picture folder: Board_Tinysgs_2.4GHz_V1
2021-07-01 Test implementation images in README
2021-07-01 README Changes and rename Lib & Fp folder name
    Change of "Lib & empreinte" into "Lib & Fp" folder name
    README Changes
2021-07-09 Update README Board
    Update comming:
    Kicad board project
    Picture
    mikrobus E28 / Lambda80C board
2021-07-15 README + new picture
    Kicad project will come later
    + Lambda80 module
    + E28m odule
    Need more description about the pin and sofware
2021-07-19 Push board_V1 project
2021-07-19 Adding Board_Tinysgs README
2021-07-19 E28 project
2021-07-19 Rename E28 project + picture
2021-07-19 Lambda80 mikrobus board project
2021-07-19 fix (minor)
2021-07-20 Update README + Doc
2021-07-23 add images of pcbs
2021-07-23 rotate images
2021-07-23 update image
2021-07-23 add gitignore
2021-07-26 Update images Board_V1
2021-07-28 Firmware firts commit
2021-07-28 LSM6DS3_Accelerometer_Gyroscope - README update
2021-07-29 add miromico; fix items
2021-07-29 add url
2021-07-29 add SX1280PATR24
2021-07-29 add ref; add sections
2021-07-29 add refto grove boards
2021-07-29 fix title and description
2021-07-30 Adding Transceiver_modules-RadioLib
2021-07-30 Adding Transceiver_modules-SX12XX
2021-07-30 Update README and picture
2021-09-09 change images order
2021-09-13 add section on modules
2021-09-13 add e28 versions
2021-09-13 add images
2021-09-13 add image
2021-09-17 add dir for Arduino sketches
2021-09-17 move files
2021-09-17 add images of ESP32-WROOM-32U-38pins
2021-09-17 add ref
2021-09-17 add settings
2021-09-20 add link to https://jlcpcb.com/
2021-11-14 remove Settings.h
2021-11-14 remove imported library
2021-11-14 add simple sketckes for tx rx 2.4GHzlora messages
2021-11-14 remove external lib (RadioLib)
2021-11-14 improve readme
2021-11-14 improve ident
2021-11-15 update todo list
2021-11-15 add example for GPS
2021-11-15 remove old example of GPS
2021-11-15 init RIOT firmware
2021-11-15 add readme to TinyGPSPlus_FullExample
2021-11-15 add example for mqtt
2021-11-15 add debug mode into TinyGPSPlus_FullExample
2021-11-15 improve readme (check todos, list modules)
2021-11-15 add a example for satellite tracker
2021-11-15 reident tithe
2021-11-15 rename Vroom by Wroom
2021-11-15 reorg sections
2021-11-15 add contributor
2021-11-19 add Off-the-shelves gateways for LoRa 2.4 GHz
2021-11-19 complete Off-the-shelves gateways for LoRa 2.4 GHz
2021-11-25 add section for LR1120
2021-12-03 add todo
2021-12-03 add embit module
2021-12-14 add dirs for exported Gerber files
2021-12-14 add gerber files
2021-12-14 add gps sketch
2021-12-15 add buy section
2021-12-15 add remark
2021-12-15 add battery
2021-12-17 redo changes for section "buy"
2021-12-17 add E28 ; fix redo
2021-12-17 fix "best --> better"
2021-12-22 add ref to power
2021-12-22 add ref to Adafruit Universal USB / DC / Solar Lithium Ion/Polymer charger - bq24074
2021-12-22 add ref to Solar Power Manager Micro
2021-12-22 add images of 250_2g4_ground_stations PCB
2021-12-23 add todos
2021-12-24 add annotations for v1.1
2022-01-03 add ref for buyers
2022-01-03 improve buyers refs
2022-01-13 add dir for TinyGS
2022-01-16 remove unexisting module
2022-01-27 add images for tinygs2g4 mount party @ IUT1 Grenoble
2022-01-27 fix filename
2022-01-28 move text
2022-01-28 mv text
2022-01-28 add OpenMQTTGateway
2022-02-03 add SuperAntennaz
2022-02-08 add wio terminal
2022-02-20 add licenses section
2022-02-20 change title; add todo section
2022-03-15 add SX1280 ranging tests
2022-03-17 add ref to products
2022-03-23 change repo for pr
2022-03-24 add PPS
2022-03-24 add MicroPython
2022-03-24 add install and basic examples
2022-03-24 add GPIO
2022-03-24 move script
2022-03-24 add examples
2022-03-24 add timer example
2022-03-26 add GPS
2022-03-28 add ranging test
2022-03-28 add default board
2022-03-28 improve display
2022-03-28 add example for Grove LCD
2022-03-30 import ino and docs for Grove LoRa E5 modem
2022-04-05 init ino for X-NUCLEO-IHM02A1
2022-04-06 add section basic operations
2022-04-06 add image for basic operations
2022-04-06 add ref to ANR POUCET
2022-04-15 adapt GroveLoRaE5.ino for TinyGS
2022-04-26 add test for SDCard reader
2022-04-29 add olimex ESP32
2022-05-19 add example for RN2XX3 LoRaWAN modem
2022-10-10 add lr1120
2023-01-09 add todo for https://fr.rs-online.com/web/p/lpwan/9033059
2023-01-10 add more images
2023-01-12 add image with rtk moduel
2023-01-19 add dir for zephyr
2023-01-21 add Abeeway-Murata geoloc module
2023-02-02 fix todo
2024-03-19 add ppk2
2024-03-19 fix typo
2024-03-21 add contrib from Nicolas Nohlier
2024-03-21 add Nicerf TXCO
2024-03-21 add new contributors
2024-04-10 add config for very long range experiments with stratospheric balloons
2024-04-10 improve trace
2024-04-13 fix buffer size
2024-04-13 init RS485 5 Click
2024-04-13 init CAN
2024-04-13 add click analyzer
2024-04-13 init Analog MUX Click
2024-04-13 init ADC boards
2024-04-15 add macAddress; variable tx_power
2024-04-15 add frame collisions
2024-04-15 add new class implementing LoRa SyncWord
2024-04-16 add syncword to receiver; change packet trace in receiver
2024-04-17 add module for Arduino_UNO_click_shield
2024-04-25 add antennas sections
2024-04-25 add sirio 2.4 Ghz antenna
2024-06-20 init dir for RTC
2024-06-26 clean SettingsModule.h and add MIKROBUS0_NICERF configuration
2024-06-26 add MultiConfig example
2024-09-26 add sketch for GroveTemperatureHumidity_TH02 module
2024-09-26 add short tuto for power monitoring
2025-04-01 init RadioLib
2025-04-07 fix pin
2025-04-07 add define for showing GNSS data
2025-04-07 add poi
2025-04-07 add trace
2025-04-07 init PPS sketch
2025-04-26 init Mikrobus adapter for Microchip RN2483 module
2025-04-30 add simple TX RX for radiolib with SX1280 Lambda80
2025-04-30 improve traces
2025-04-30 add radiolib example for ranging
2025-05-01 add sketch for FLRC
2025-05-01 add debug defines for RadioLib
2025-05-01 add CAD; add debug defines for RadioLib
2025-05-01 add debug for RL; change default SF
2025-05-01 add debug for RL
2025-05-01 set SF to 5
2025-05-01 move CC1101
2025-05-01 init CC1101 for ESP32
2025-05-03 fix pinout
2025-05-03 import and customize transmit sketch
2025-05-03 import and customize sketch for receiving
2025-05-03 import and customize sketch for setting radio
2025-05-03 import and customize sketch for scan frequencies
2026-03-09 init dir for platformio
2026-03-18 init lr2021 sketches
2026-03-18 Update supported lists
